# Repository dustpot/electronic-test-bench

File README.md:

# Electronic Test Bench (ETB)

A Raspberry Pi 4 bench instrument built for ECSE 2920 (Design Methodology) at the University of Georgia, Spring 2026. It includes a function generator, ohmmeter, voltmeter, DC voltage reference, and frequency meter, all controlled with a rotary encoder and a 20×4 LCD.

This was a five-person team project. Original course repository: [Herring-UGAECSE-2920-S26/Group-4](https://github.com/Herring-UGAECSE-2920-S26/Group-4)

## My role

- Designed the ohmmeter and the square-wave generator
- Did the system integration for Checkpoint B and Checkpoint A-
- Built the sine-wave generator and frequency meter for the final checkpoint
- Updated the schematics and PCB for the final checkpoint

## Instruments

| Instrument | Range | How it works |
| --- | --- | --- |
| Square wave | 100 Hz – 10 kHz | Pi hardware PWM (GPIO18) → MCP4131 digipot → TL084 amplifier |
| Sine wave | 1 – 10 kHz, 0 – 10 Vpp | DMA-timed PWM (GPIO13) → two RC low-pass filters → digipot → amplifier → DC offset stage |
| Ohmmeter | 500 Ω – 10 kΩ | Wheatstone bridge with an MCP4131 as the adjustable arm, LM339 comparator, 7-step binary search |
| Voltmeter | ±5 V | 6-bit SAR ADC (R-2R ladder + LM339), 5-reading majority vote per bit |
| DC reference | ±5 V | 6-bit R-2R ladder → TL084 level-shift and gain stage |
| Frequency meter | 1 – 10 kHz | LM339 comparator with hysteresis → GPIO24, rising-edge timestamps with pigpio |
| Power | 24 V in, ±12 V out | Virtual ground at 12 V, op-amp-driven MOSFET push-pull stage |

The user interface is a menu state machine driven entirely by a KY-040 rotary encoder (turn to move, press to select).

## Results

Measured during Checkpoint B testing.

| Instrument | Result |
| --- | --- |
| Ohmmeter | 5.5% average error across 10 resistors, 220 Ω – 10 kΩ |
| Square wave | Frequency within 0.04% of target, 100 Hz – 10 kHz |
| Voltmeter | Within 0.25 V of the source, −5 V to +5 V |
| DC reference | Within 0.1 V of the setpoint, −5 V to +3.1 V |

## Repository layout

```
electronic-test-bench/
├── README.md
├── software/
│   ├── checkA_main.py
│   ├── adc.py
│   ├── digipot_dual.py
│   ├── freq_measure.py
│   ├── inputs.py
│   ├── lcd.py
│   └── requirements.txt
├── hardware/
│   ├── kicad/              # .kicad_pro, .kicad_sch, .kicad_pcb
│   └── schematics/         # PDF export of each subsystem
├── data/                   # calibration and test measurements (.csv)
└── docs/
    ├── ETB_Technical_Documentation.pdf
    └── images/
```

## Running it

Requires a Raspberry Pi 4 with Python 3, SPI and I²C enabled.

```
sudo pigpiod
pip install -r software/requirements.txt
python3 software/checkA_main.py
```

## Documentation

Full design writeup: [docs/ETB_Technical_Documentation.pdf](docs/ETB_Technical_Documentation.pdf)

User manual: [docs/User Manual.pdf](docs/User%20Manual.pdf)

## Team

Avery Dedjoe, Allan Gramajo, Justin Park, Samuel Baker, Jakob Braski

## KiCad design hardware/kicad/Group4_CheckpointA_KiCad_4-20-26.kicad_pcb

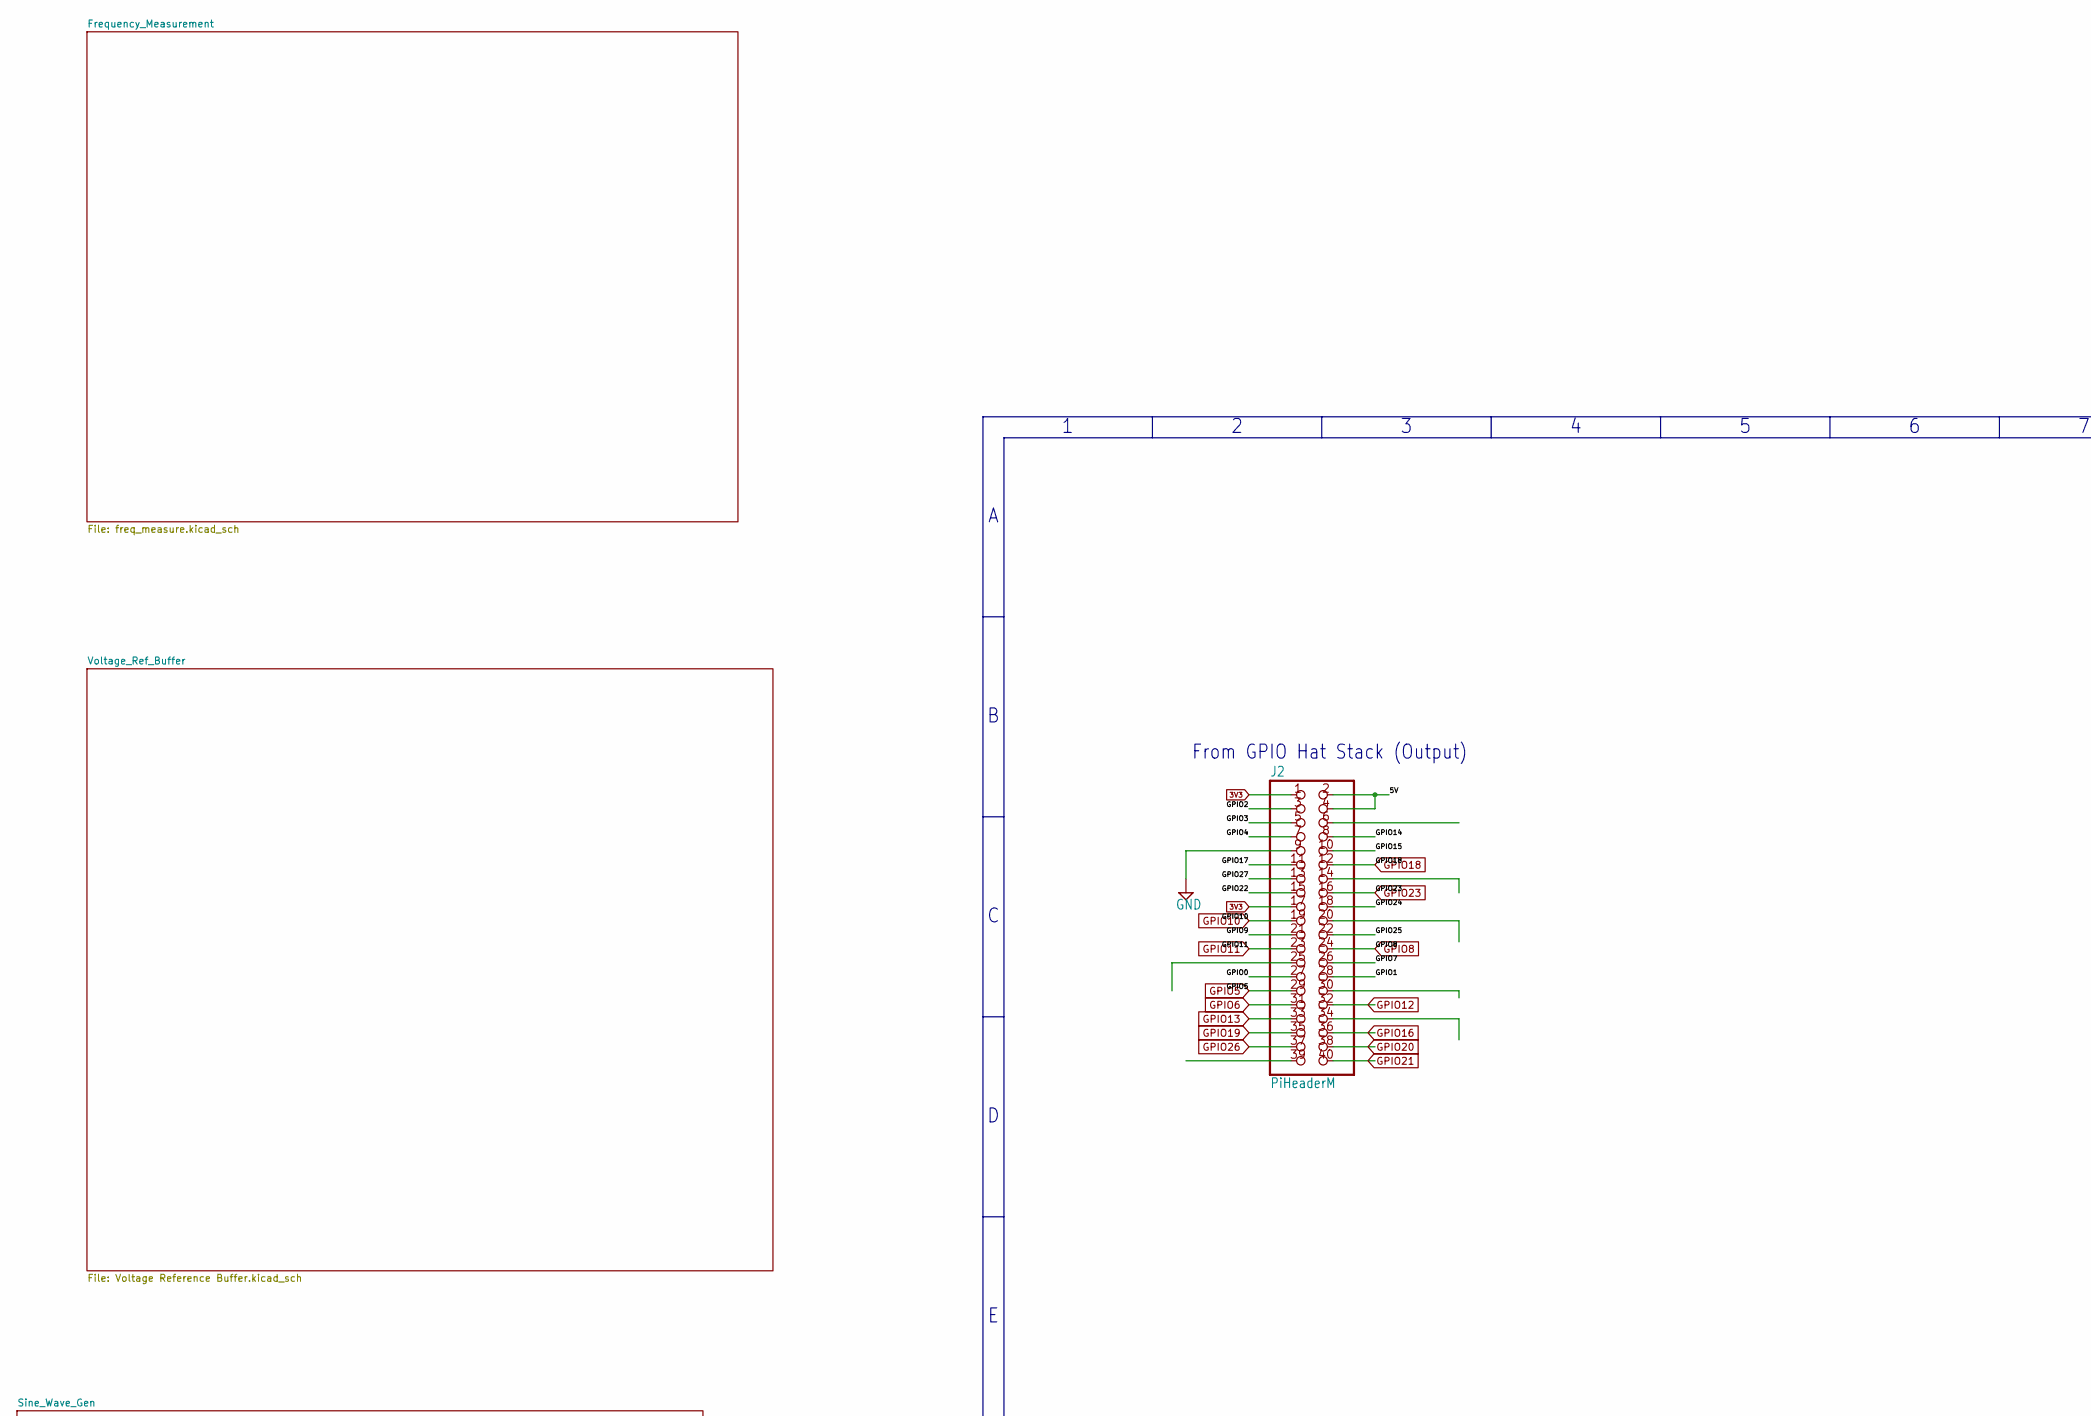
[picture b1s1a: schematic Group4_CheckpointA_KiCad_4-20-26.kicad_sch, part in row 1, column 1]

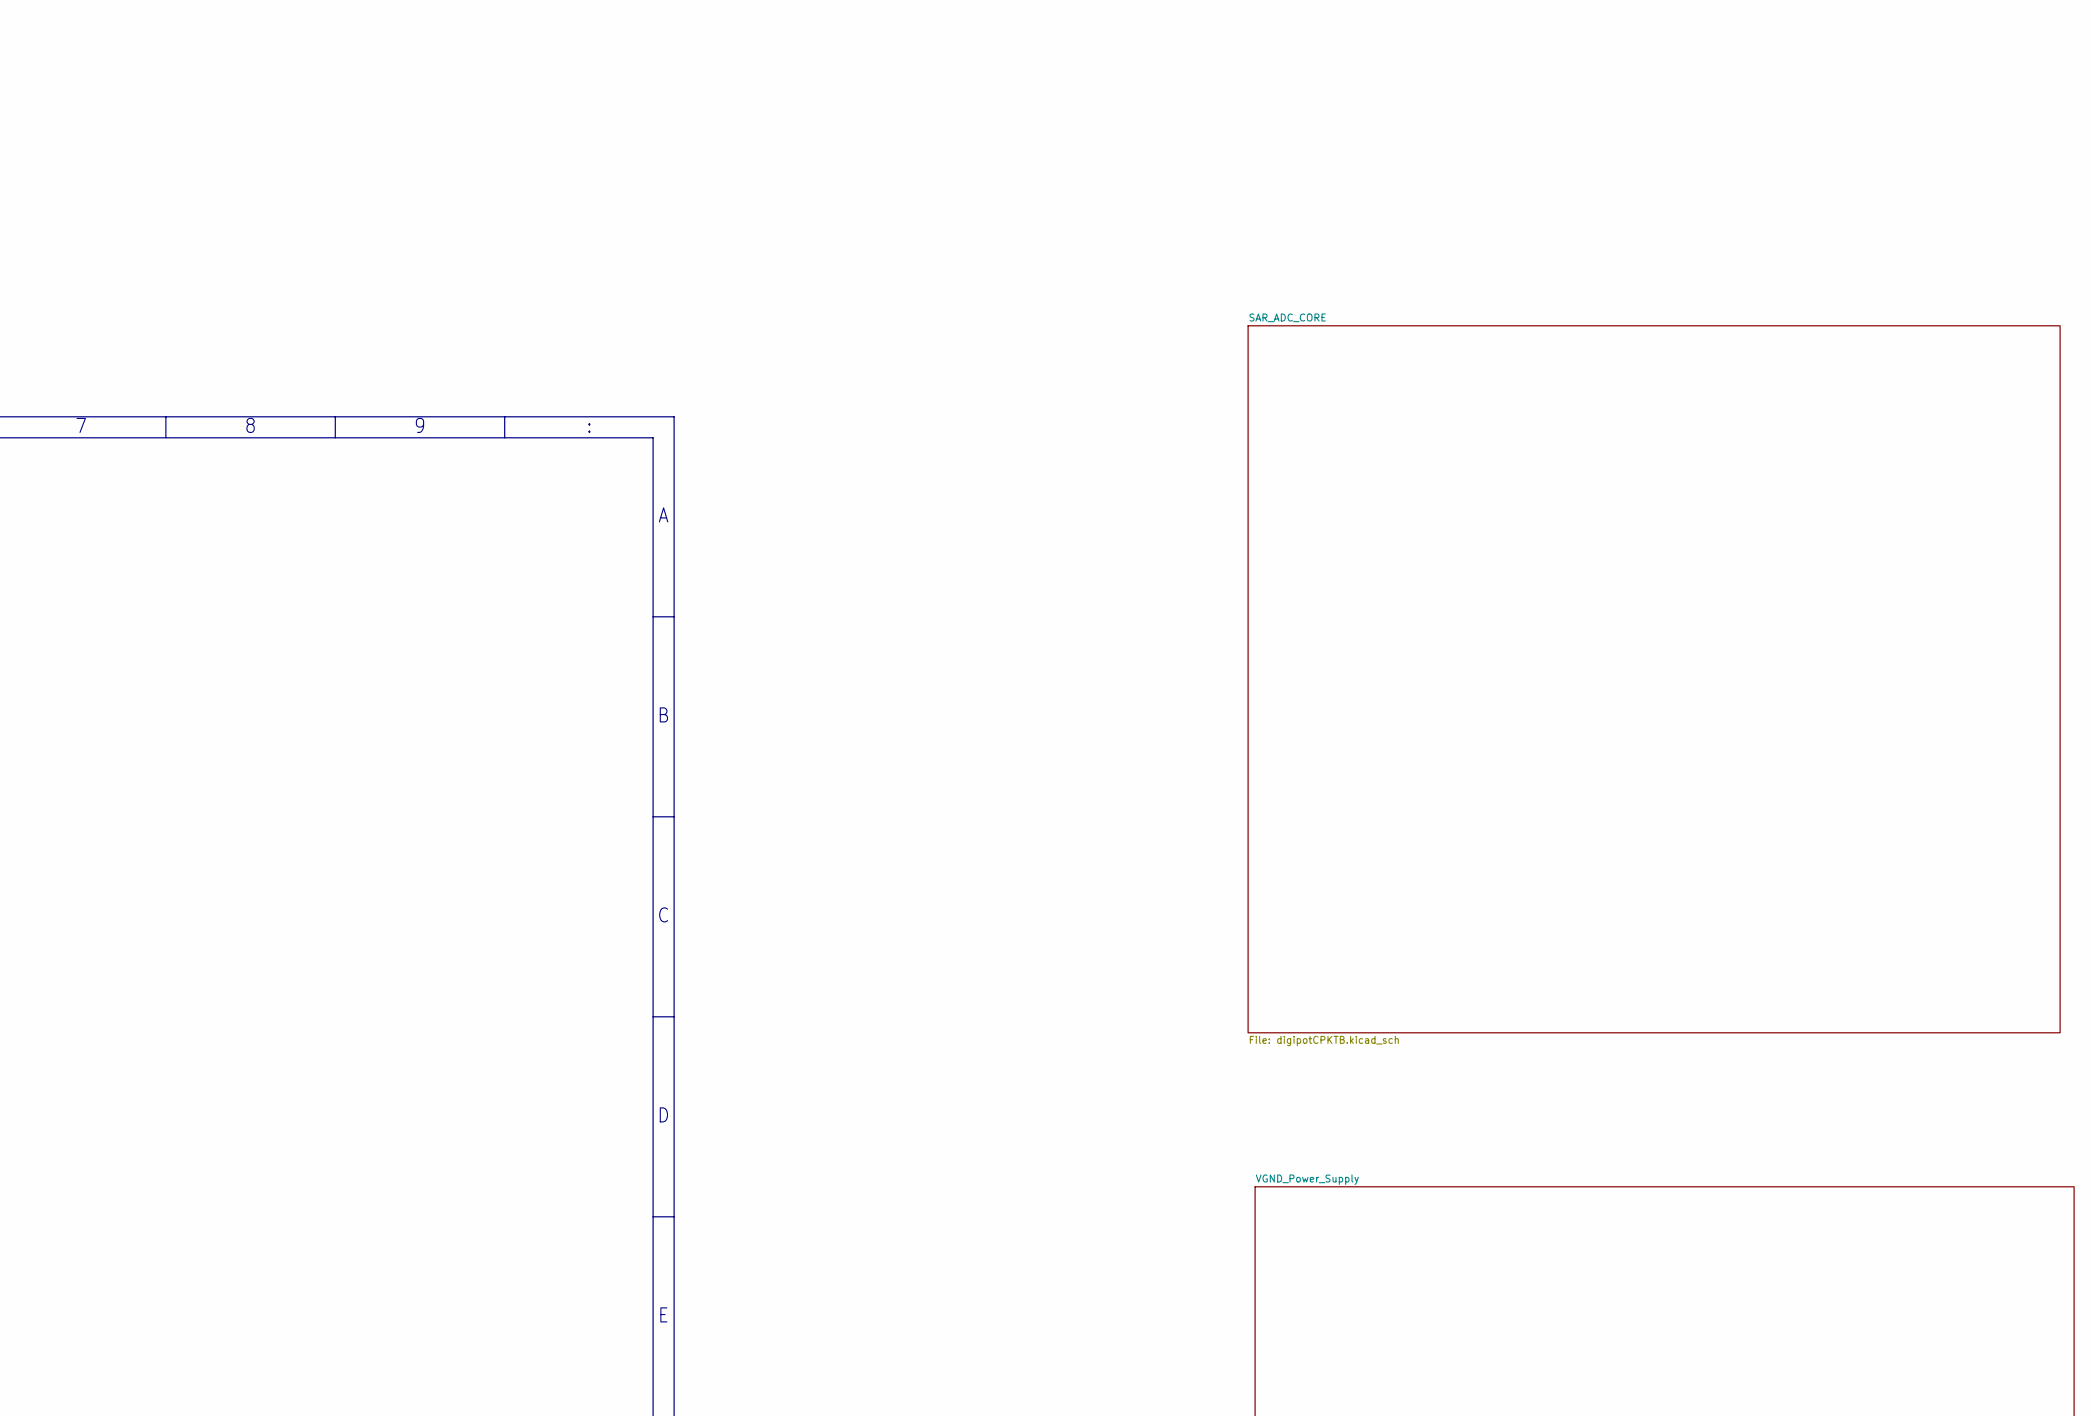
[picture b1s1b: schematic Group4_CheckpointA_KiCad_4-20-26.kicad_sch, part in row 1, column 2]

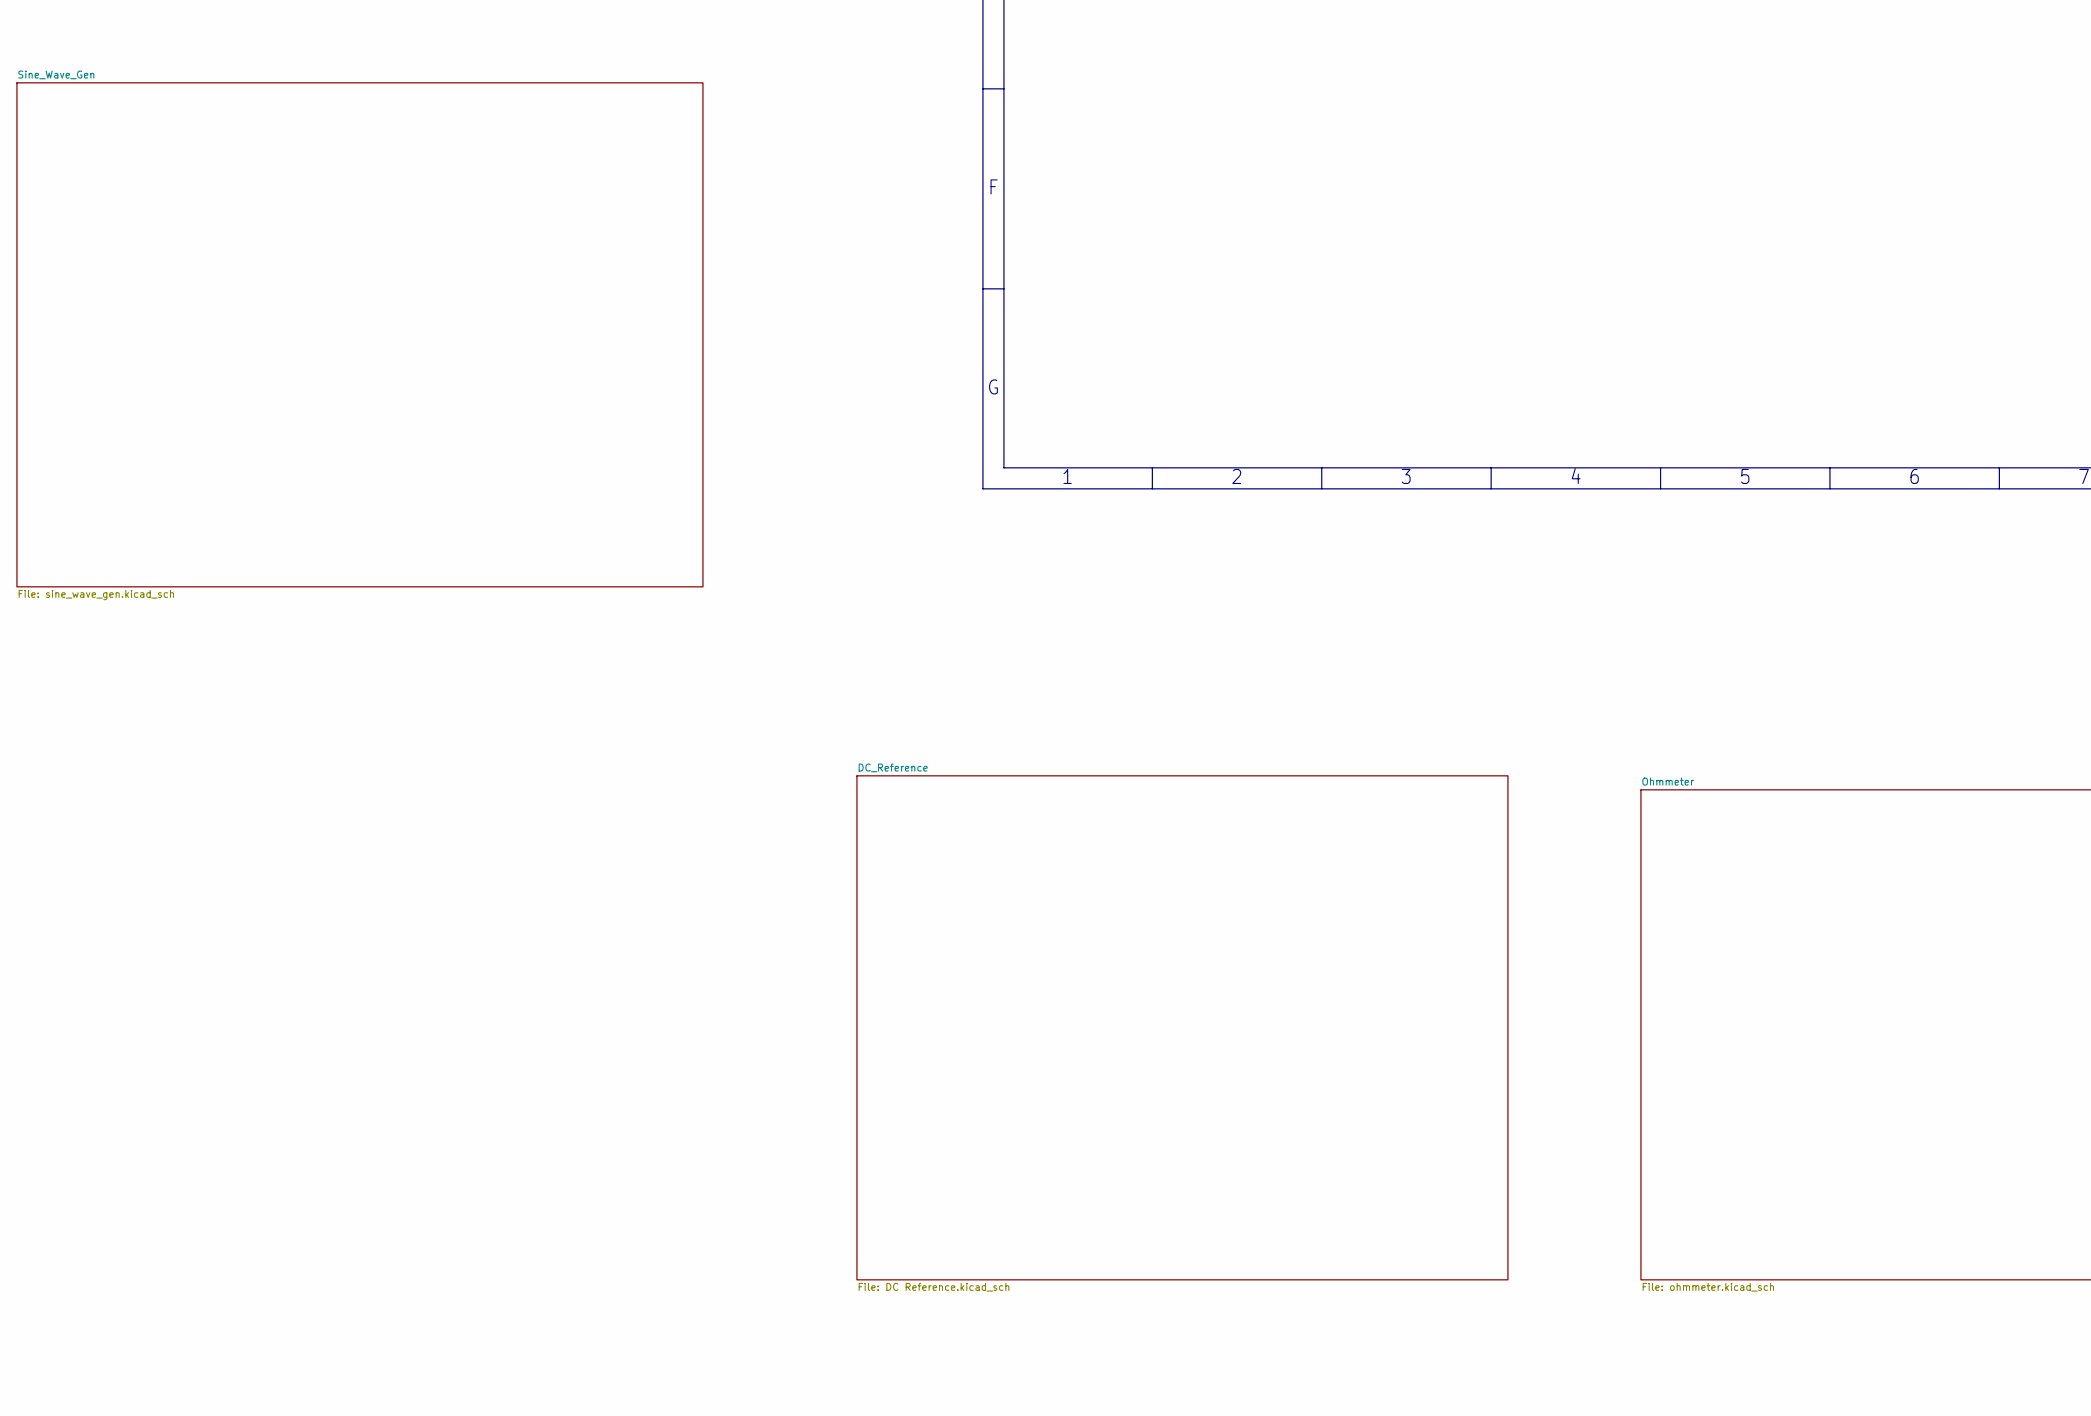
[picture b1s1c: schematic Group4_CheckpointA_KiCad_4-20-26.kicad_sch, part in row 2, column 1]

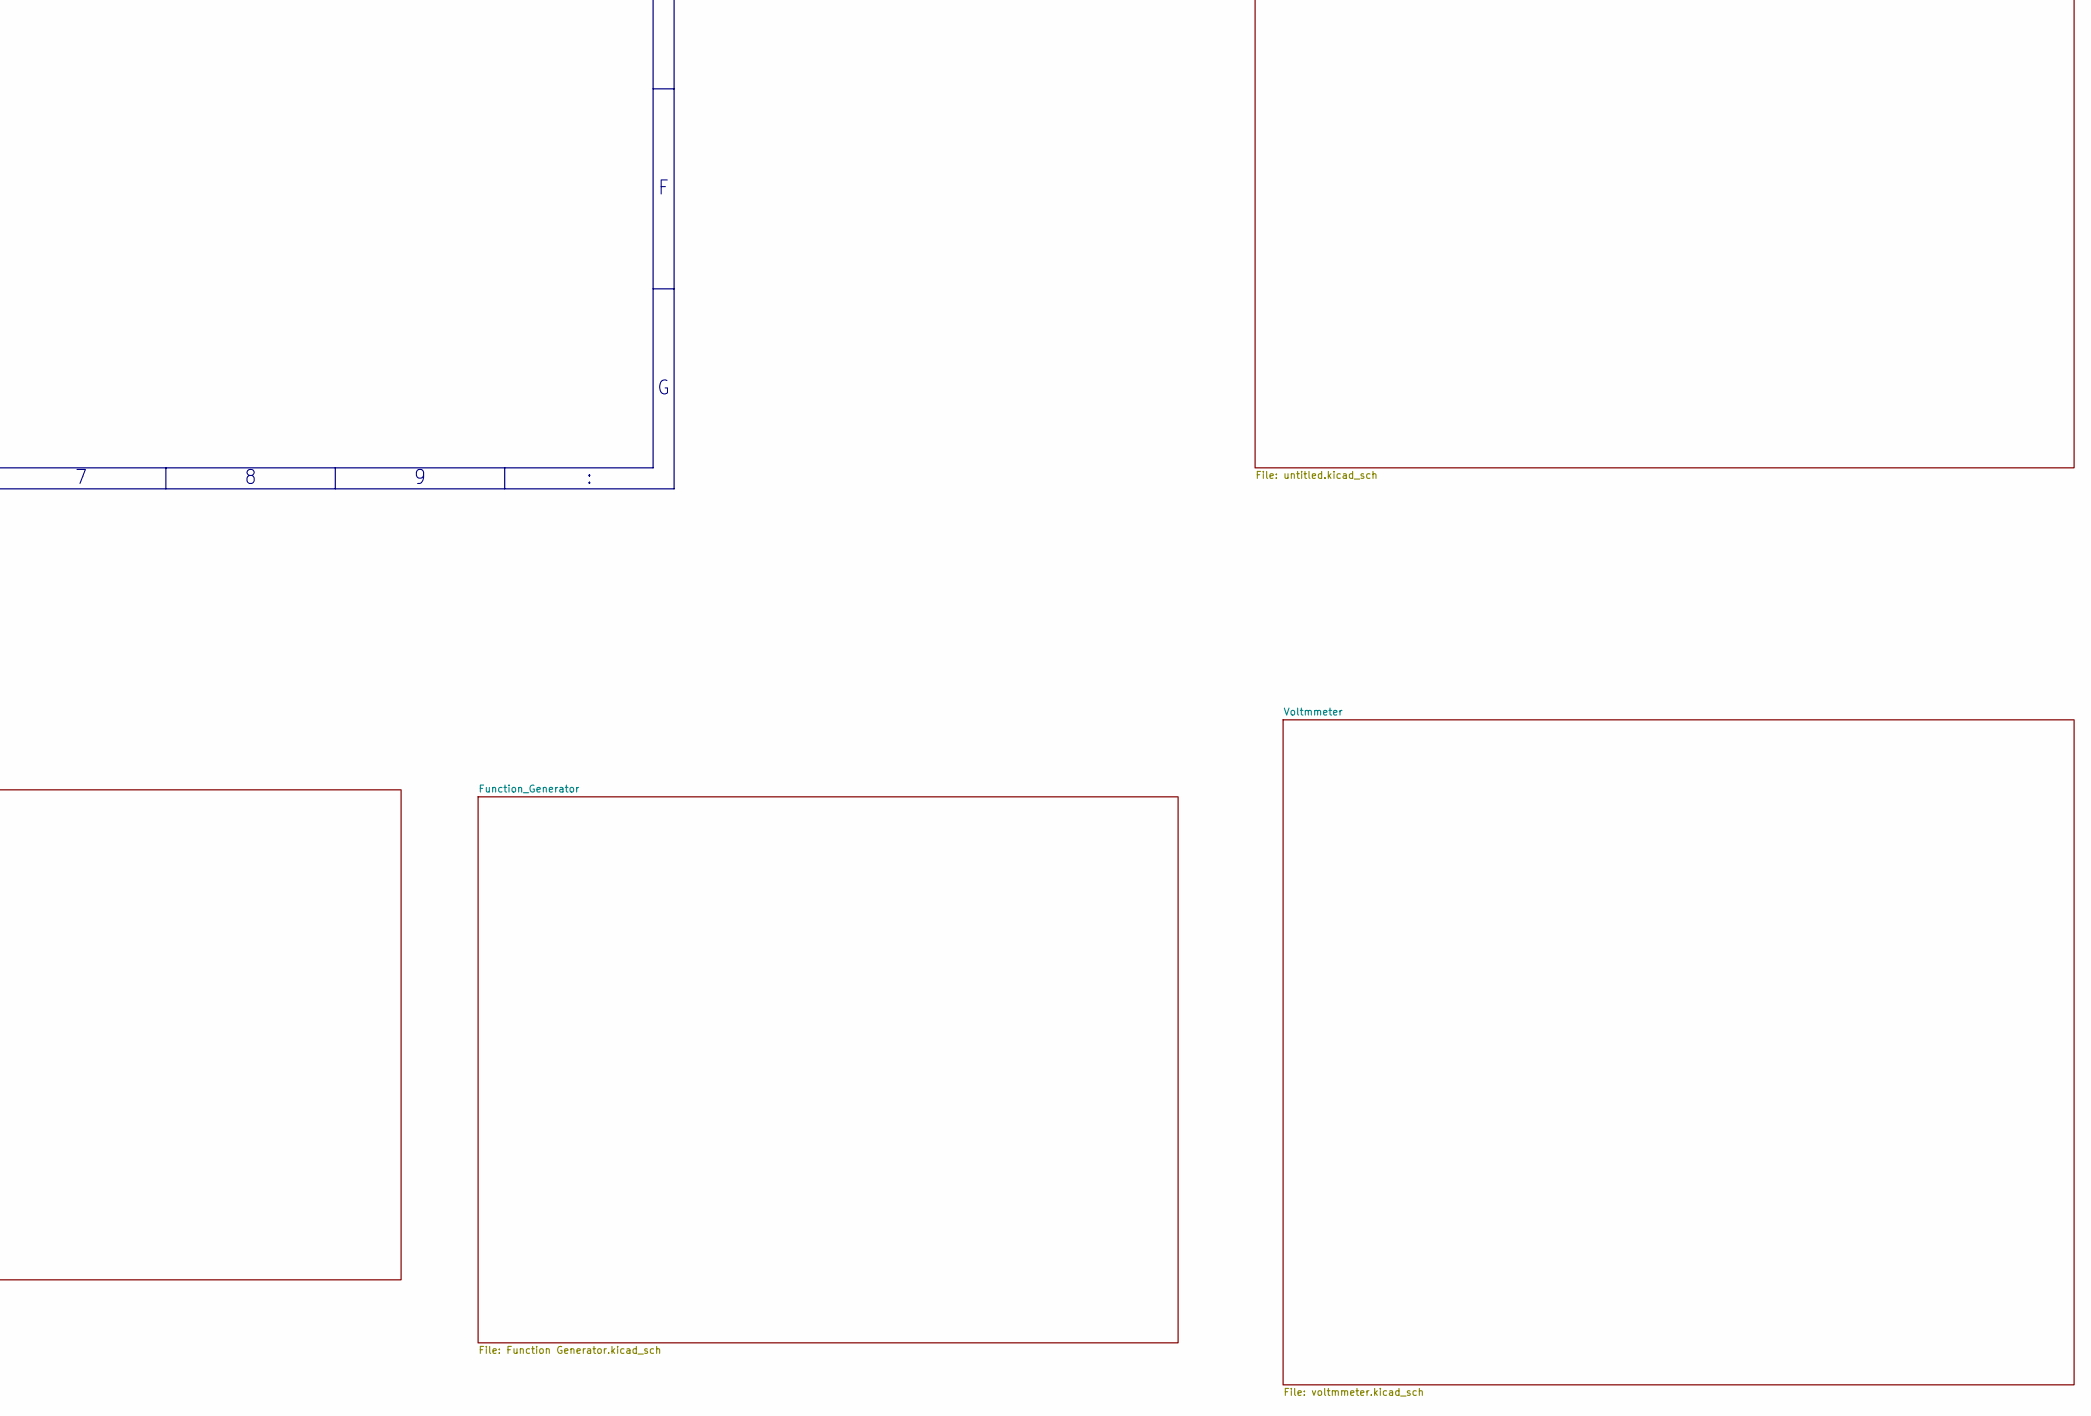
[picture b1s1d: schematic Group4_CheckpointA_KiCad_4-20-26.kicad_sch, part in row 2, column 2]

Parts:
J2: PiHeaderM; PinHeader_2x20_P2.54mm_Vertical

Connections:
3V3: J2.1, J2.17
-12: J2.9; also elsewhere on the board
/5V: J2.2, J2.4
/GPIO0: J2.27
/GPIO1: J2.28
/GPIO2: J2.3
/GPIO3: J2.5
/GPIO4: J2.7
/GPIO7: J2.26
/GPIO9: J2.21
/GPIO14: J2.8
/GPIO15: J2.10
/GPIO17: J2.11
/GPIO22: J2.15
/GPIO24: J2.18
/GPIO25: J2.22
/GPIO27: J2.13
GPIO5: J2.29; also elsewhere on the board
GPIO6: J2.31
GPIO8: J2.24; also elsewhere on the board
GPIO10: J2.19; also elsewhere on the board
GPIO11: J2.23; also elsewhere on the board
GPIO12: J2.32; also elsewhere on the board
GPIO13: J2.33; also elsewhere on the board
GPIO16: J2.36; also elsewhere on the board
GPIO18: J2.12; also elsewhere on the board
GPIO19: J2.35; also elsewhere on the board
GPIO20: J2.38; also elsewhere on the board
GPIO21: J2.40; also elsewhere on the board
GPIO23: J2.16; also elsewhere on the board
GPIO26: J2.37

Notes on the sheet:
From GPIO Hat Stack (Output)

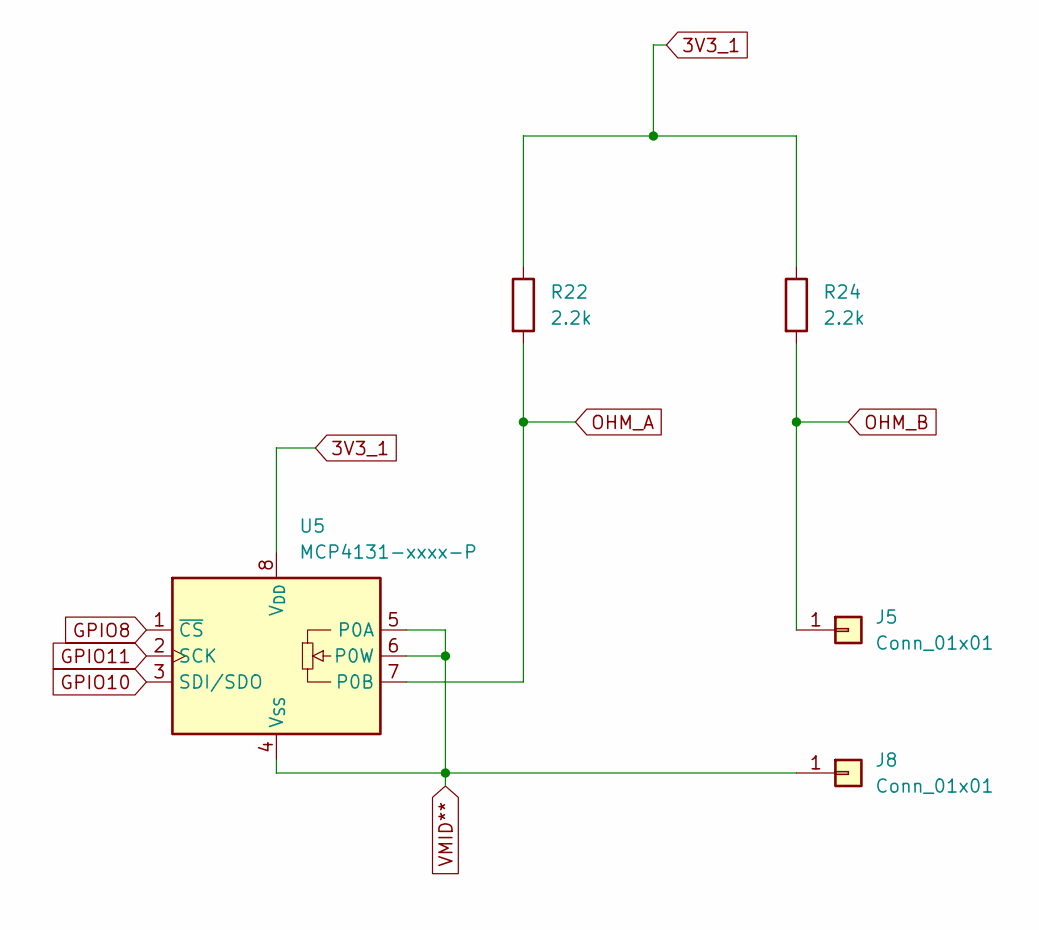
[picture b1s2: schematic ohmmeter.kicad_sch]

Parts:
J5, J8: Conn_01x01; PinHeader_1x01_P2.54mm_Vertical
R22, R24: 2.2k; R_Axial_DIN0207_L6.3mm_D2.5mm_P2.54mm_Vertical
U5: MCP4131-xxxx-P; DIP-8_W7.62mm

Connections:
3V3_1: R22.1, R24.1, U5.8 (V_{DD}); also elsewhere on the board
GPIO8: U5.1 (~CS); also elsewhere on the board
GPIO10: U5.3 (SDI/SDO); also elsewhere on the board
GPIO11: U5.2 (SCK); also elsewhere on the board
OHM_A: R22.2, U5.7 (P0B); also elsewhere on the board
OHM_B: J5.1, R24.2; also elsewhere on the board
VMID**: J8.1, U5.4 (V_{SS}), U5.5 (P0A), U5.6 (P0W); also elsewhere on the board

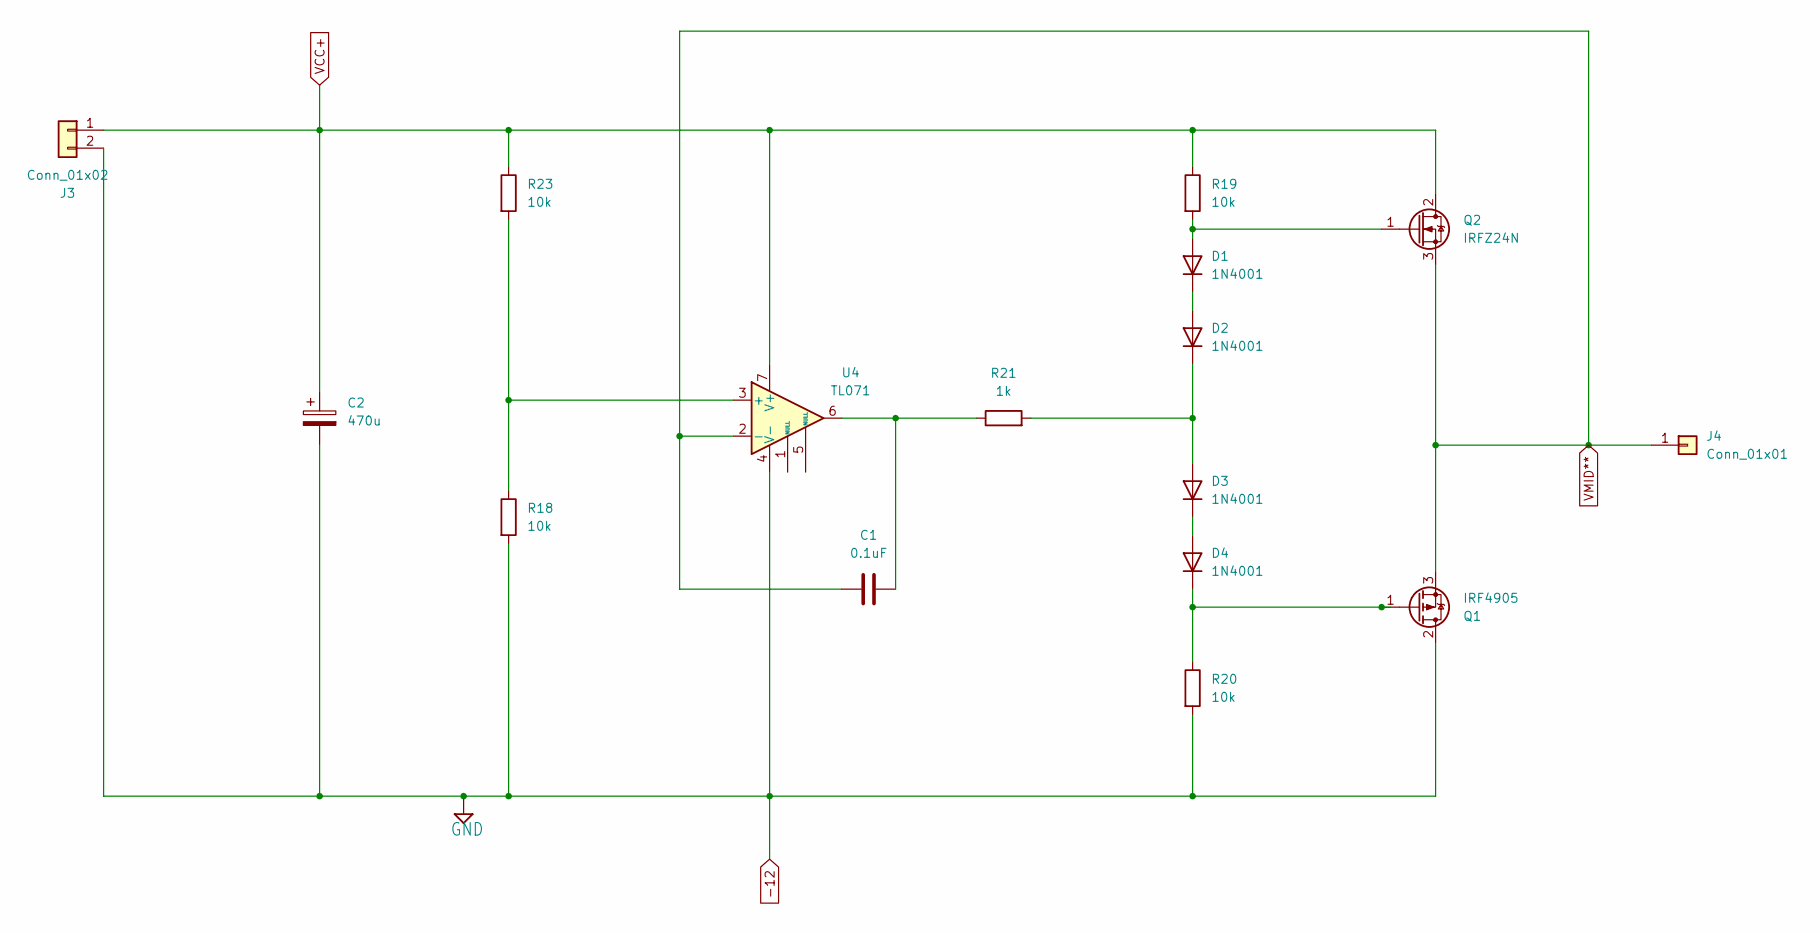
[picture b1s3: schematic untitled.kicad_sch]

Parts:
C1: 0.1uF; C_Disc_D5.0mm_W2.5mm_P2.50mm
C2: 470u; CP_Radial_D10.0mm_P5.00mm
D1, D2, D3, D4: 1N4001; D_DO-41_SOD81_P10.16mm_Horizontal
J3: Conn_01x02; PinHeader_1x02_P2.54mm_Vertical
J4: Conn_01x01; PinHeader_1x01_P2.54mm_Vertical
Q1: IRF4905; TO-220-3_Vertical
Q2: IRFZ24N; TO-220-3_Vertical
R18, R19, R20, R23: 10k; R_Axial_DIN0207_L6.3mm_D2.5mm_P2.54mm_Vertical
R21: 1k; R_Axial_DIN0207_L6.3mm_D2.5mm_P2.54mm_Vertical
U4: TL071; DIP-8_W7.62mm

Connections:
-12: C2.2, J3.2, Q1.2 (D), R18.2, R20.2, U4.4 (V-); also elsewhere on the board
unnamed: C1.2, R21.1, U4.6
unnamed: D1.2 (A), Q2.1 (G), R19.2
unnamed: D1.1 (K), D2.2 (A)
unnamed: D2.1 (K), D3.2 (A), R21.2
unnamed: D3.1 (K), D4.2 (A)
unnamed: D4.1 (K), Q1.1 (G), R20.1
unnamed: R18.1, R23.2, U4.3 (+)
VCC+: C2.1, J3.1, Q2.2 (D), R19.1, R23.1, U4.7 (V+); also elsewhere on the board
VMID**: C1.1, J4.1, Q1.3 (S), Q2.3 (S), U4.2 (-); also elsewhere on the board

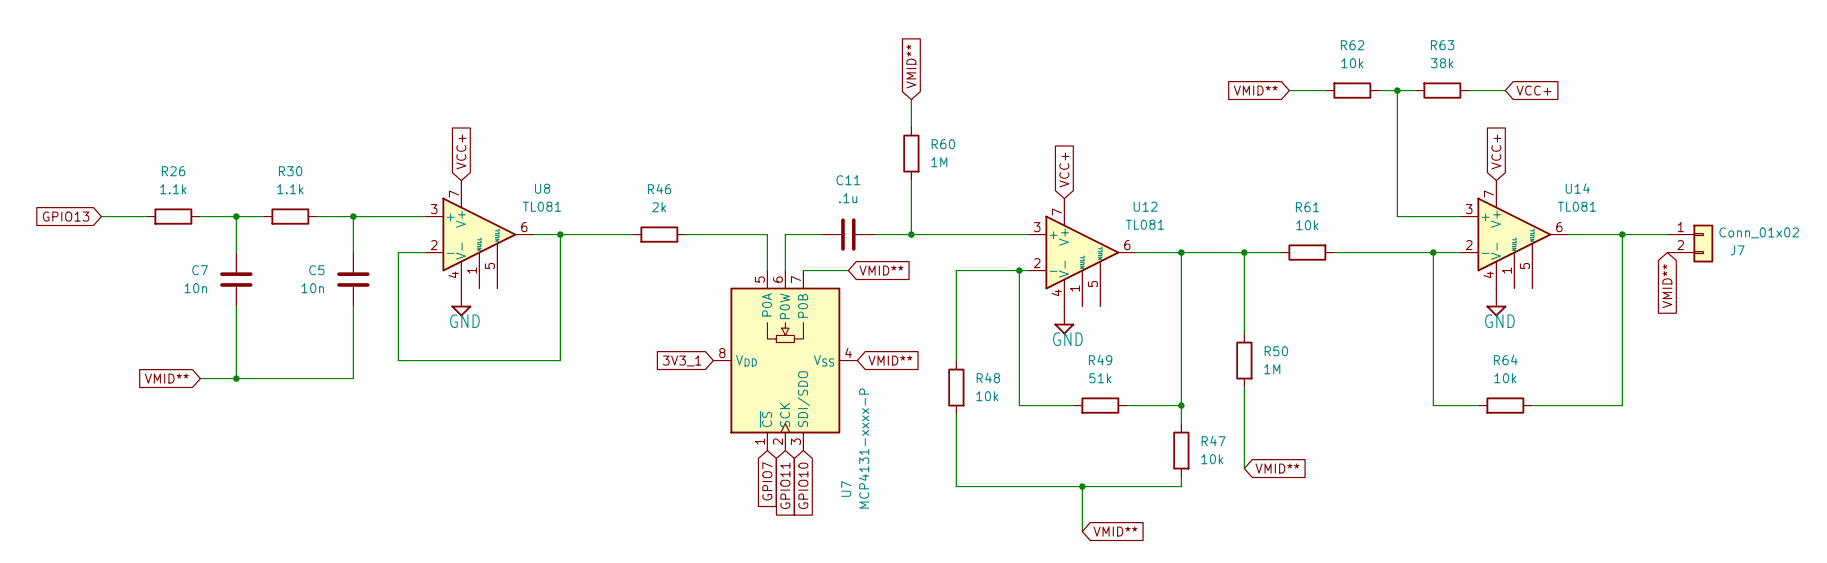
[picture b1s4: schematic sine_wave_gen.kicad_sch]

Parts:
C5, C7: 10n; C_Disc_D5.0mm_W2.5mm_P2.50mm
C11: .1u; C_Disc_D5.0mm_W2.5mm_P2.50mm
J7: Conn_01x02; PinHeader_1x02_P2.54mm_Vertical
R26, R30: 1.1k; R_Axial_DIN0207_L6.3mm_D2.5mm_P2.54mm_Vertical
R46: 2k; R_Axial_DIN0207_L6.3mm_D2.5mm_P2.54mm_Vertical
R47, R48, R61, R62, R64: 10k; R_Axial_DIN0207_L6.3mm_D2.5mm_P2.54mm_Vertical
R49: 51k; R_Axial_DIN0207_L6.3mm_D2.5mm_P2.54mm_Vertical
R50, R60: 1M; R_Axial_DIN0207_L6.3mm_D2.5mm_P2.54mm_Vertical
R63: 38k; R_Axial_DIN0207_L6.3mm_D2.5mm_P2.54mm_Vertical
U7: MCP4131-xxxx-P; DIP-8_W7.62mm
U8, U12, U14: TL081; DIP-8_W7.62mm

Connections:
3V3_1: U7.8 (V_{DD}); also elsewhere on the board
-12: U8.4 (V-), U12.4 (V-), U14.4 (V-); also elsewhere on the board
GPIO7: U7.1 (~CS); also elsewhere on the board
GPIO10: U7.3 (SDI/SDO); also elsewhere on the board
GPIO11: U7.2 (SCK); also elsewhere on the board
GPIO13: R26.2; also elsewhere on the board
unnamed: C7.2, R26.1, R30.2
unnamed: J7.1, R64.1, U14.6
unnamed: R47.1, R49.1, R50.1, R61.1, U12.6
unnamed: R46.1, U7.5 (P0A)
unnamed: C11.2, U7.6 (P0W)
unnamed: C5.2, R30.1, U8.3 (+)
unnamed: R46.2, U8.2 (-), U8.6
unnamed: C11.1, R60.2, U12.3 (+)
unnamed: R48.1, R49.2, U12.2 (-)
unnamed: R62.1, R63.2, U14.3 (+)
unnamed: R61.2, R64.2, U14.2 (-)
VCC+: R63.1, U8.7 (V+), U12.7 (V+), U14.7 (V+); also elsewhere on the board
VMID**: C5.1, C7.1, J7.2, R47.2, R48.2, R50.2, R60.1, R62.2, U7.4 (V_{SS}), U7.7 (P0B); also elsewhere on the board

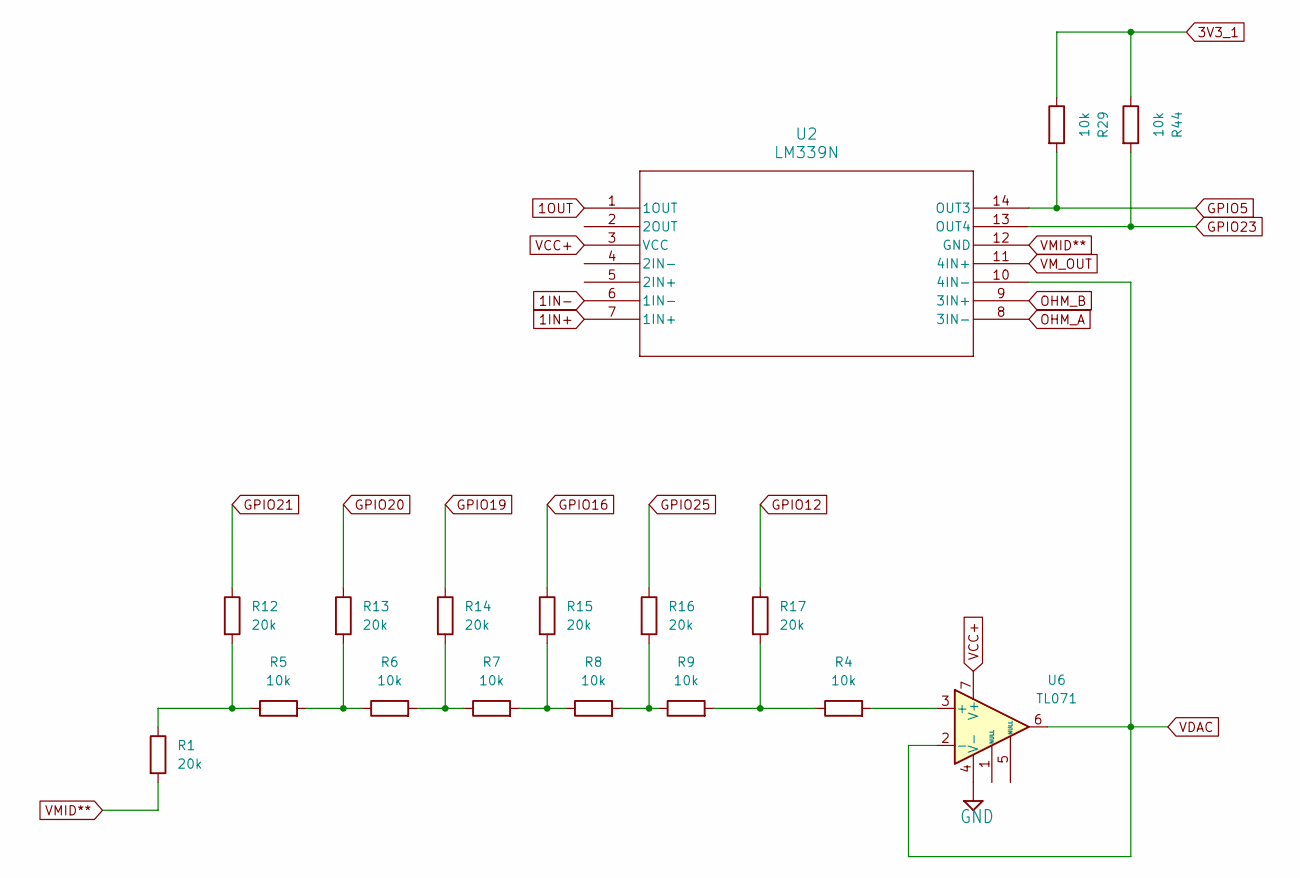
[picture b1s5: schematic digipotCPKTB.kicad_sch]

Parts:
R1, R12, R13, R14, R15, R16, R17: 20k; R_Axial_DIN0207_L6.3mm_D2.5mm_P2.54mm_Vertical
R4, R5, R6, R7, R8, R9, R29, R44: 10k; R_Axial_DIN0207_L6.3mm_D2.5mm_P2.54mm_Vertical
U2: LM339N; DIP-14_W7.62mm
U6: TL071; DIP-8_W7.62mm

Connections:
1IN+: U2.7 (1IN+); also elsewhere on the board
1IN-: U2.6 (1IN-); also elsewhere on the board
1OUT: U2.1 (1OUT); also elsewhere on the board
3V3_1: R29.1, R44.1; also elsewhere on the board
-12: U6.4 (V-); also elsewhere on the board
GPIO5: R29.2, U2.14 (OUT3); also elsewhere on the board
GPIO12: R17.1; also elsewhere on the board
GPIO16: R15.1; also elsewhere on the board
GPIO19: R14.1; also elsewhere on the board
GPIO20: R13.1; also elsewhere on the board
GPIO21: R12.1; also elsewhere on the board
GPIO23: R44.2, U2.13 (OUT4); also elsewhere on the board
GPIO25: R16.1
unnamed: R1.1, R5.1, R12.2
unnamed: R5.2, R6.1, R13.2
unnamed: R6.2, R7.1, R14.2
unnamed: R7.2, R8.1, R15.2
unnamed: R8.2, R9.1, R16.2
unnamed: R4.1, R9.2, R17.2
unnamed: R4.2, U6.3 (+)
OHM_A: U2.8 (3IN-); also elsewhere on the board
OHM_B: U2.9 (3IN+); also elsewhere on the board
VCC+: U2.3 (VCC), U6.7 (V+); also elsewhere on the board
VDAC: U2.10 (4IN-), U6.2 (-), U6.6; also elsewhere on the board
VMID**: R1.2, U2.12 (GND); also elsewhere on the board
VM_OUT: U2.11 (4IN+); also elsewhere on the board

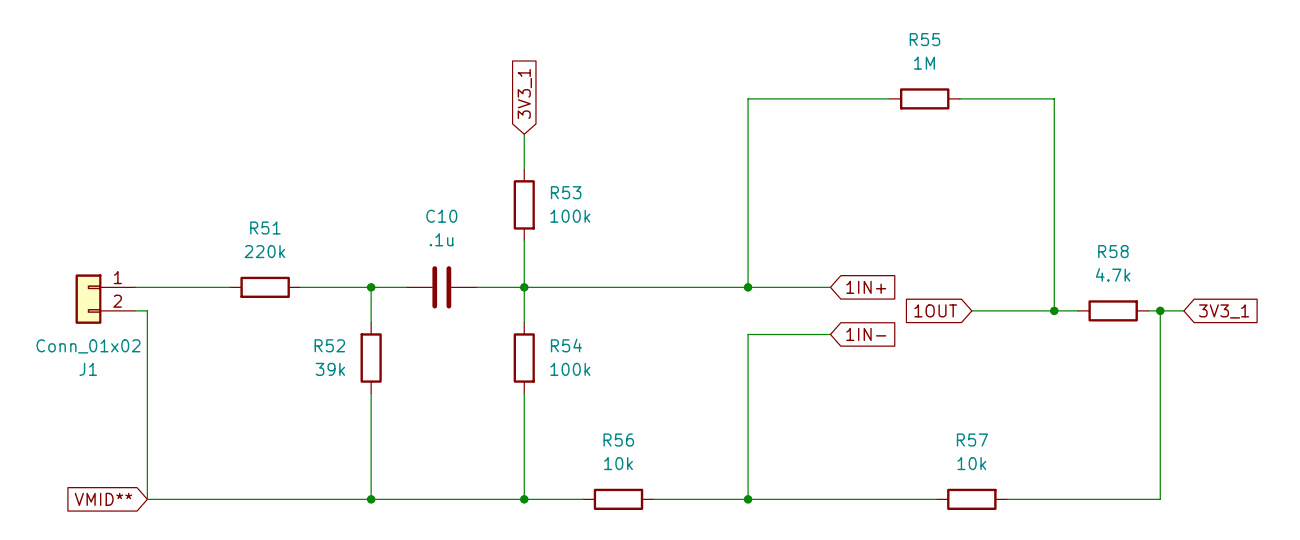
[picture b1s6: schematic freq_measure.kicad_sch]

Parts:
C10: .1u; C_Disc_D5.0mm_W2.5mm_P2.50mm
J1: Conn_01x02; PinHeader_1x02_P2.54mm_Vertical
R51: 220k; R_Axial_DIN0207_L6.3mm_D2.5mm_P2.54mm_Vertical
R52: 39k; R_Axial_DIN0207_L6.3mm_D2.5mm_P2.54mm_Vertical
R53, R54: 100k; R_Axial_DIN0207_L6.3mm_D2.5mm_P2.54mm_Vertical
R55: 1M; R_Axial_DIN0207_L6.3mm_D2.5mm_P2.54mm_Vertical
R56, R57: 10k; R_Axial_DIN0207_L6.3mm_D2.5mm_P2.54mm_Vertical
R58: 4.7k; R_Axial_DIN0207_L6.3mm_D2.5mm_P2.54mm_Vertical

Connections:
1IN+: C10.1, R53.2, R54.1, R55.2; also elsewhere on the board
1IN-: R56.2, R57.1; also elsewhere on the board
1OUT: R55.1, R58.1; also elsewhere on the board
3V3_1: R53.1, R57.2, R58.2; also elsewhere on the board
unnamed: C10.2, R51.1, R52.2
unnamed: J1.1, R51.2
VMID**: J1.2, R52.1, R54.2, R56.1; also elsewhere on the board
